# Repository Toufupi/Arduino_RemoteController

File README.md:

# Arduino_RemoteController

## ProjectDescrie 项目说明
本项目使用Arduino开发，硬件平台基于Arduino nano 与nrf24l01开发，在使用天线的情况下可以实现3KM的遥控距离

Arduino + Nrf24l01+

## Dir 目录说明
1. 分为项目控制软件代码（0.SourceCode），PCB源文件（使用kicad绘制，1.PCB）
2. 各自目录中均含有说明文件

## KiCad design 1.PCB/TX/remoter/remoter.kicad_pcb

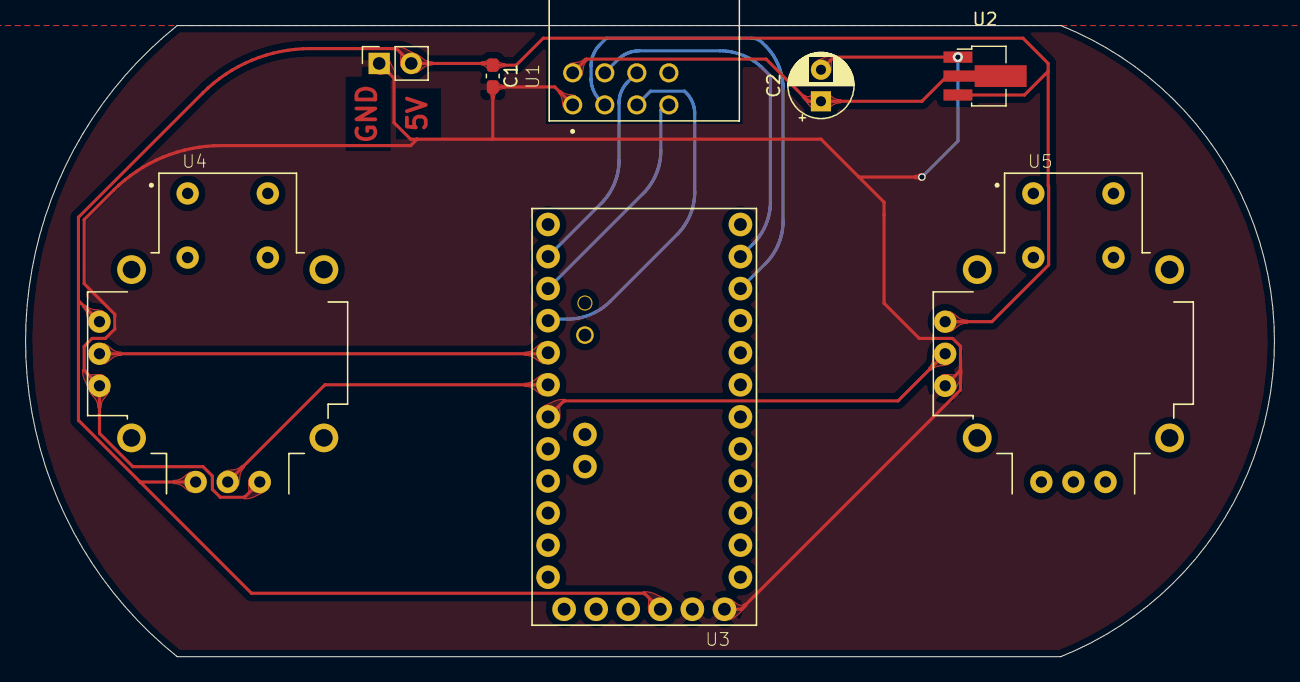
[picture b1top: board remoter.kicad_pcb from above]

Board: 2 copper layers, 98.9 x 50.0 mm, 8 parts (0 on the bottom side), 13 nets.

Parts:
C1: C_Small; C_0603_1608Metric_Pad1.08x0.95mm_HandSolder
C2: C_Small; CP_Radial_D5.0mm_P2.50mm
J1: Conn_01x02; PinSocket_1x02_P2.54mm_Vertical
U1: NRF24L01P-MODULE-PCB; XCVR_NRF24L01P-MODULE-PCB
U2: AP1117-33; SOT-89-3_Handsoldering
U3: ARDUINO_PRO_MINI; MODULE_ARDUINO_PRO_MINI
U4, U5: COM-09032; XDCR_COM-09032

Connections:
/5V: C1.1, J1.2, U2.3, U3.JP1_4, U4.H1, U4.V1, U5.V1
GND: C1.2, C2.2, J1.1, U1.1, U2.1, U3.JP1_5, U3.JP1_6, U4.H3, U4.V3, U5.V3
unnamed: C2.1, U1.2, U2.2
unnamed: U1.3, U3.JP7_3
unnamed: U1.4, U3.JP7_2
unnamed: U1.5, U3.JP6_9
unnamed: U1.6, U3.JP6_11
unnamed: U1.7, U3.JP6_10
unnamed: U3.JP6_6, U5.V2
unnamed: U3.JP6_7, U3.JP7_8, U4.H2
unnamed: U3.JP6_8, U4.V2
unnamed: U4.S1, U4.S2, U4.S3, U4.S4
unnamed: U5.S1, U5.S2, U5.S3, U5.S4

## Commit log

2021-03-03 working V0.0
2021-03-03 finish file structure
2022-02-24 addFreqJump
